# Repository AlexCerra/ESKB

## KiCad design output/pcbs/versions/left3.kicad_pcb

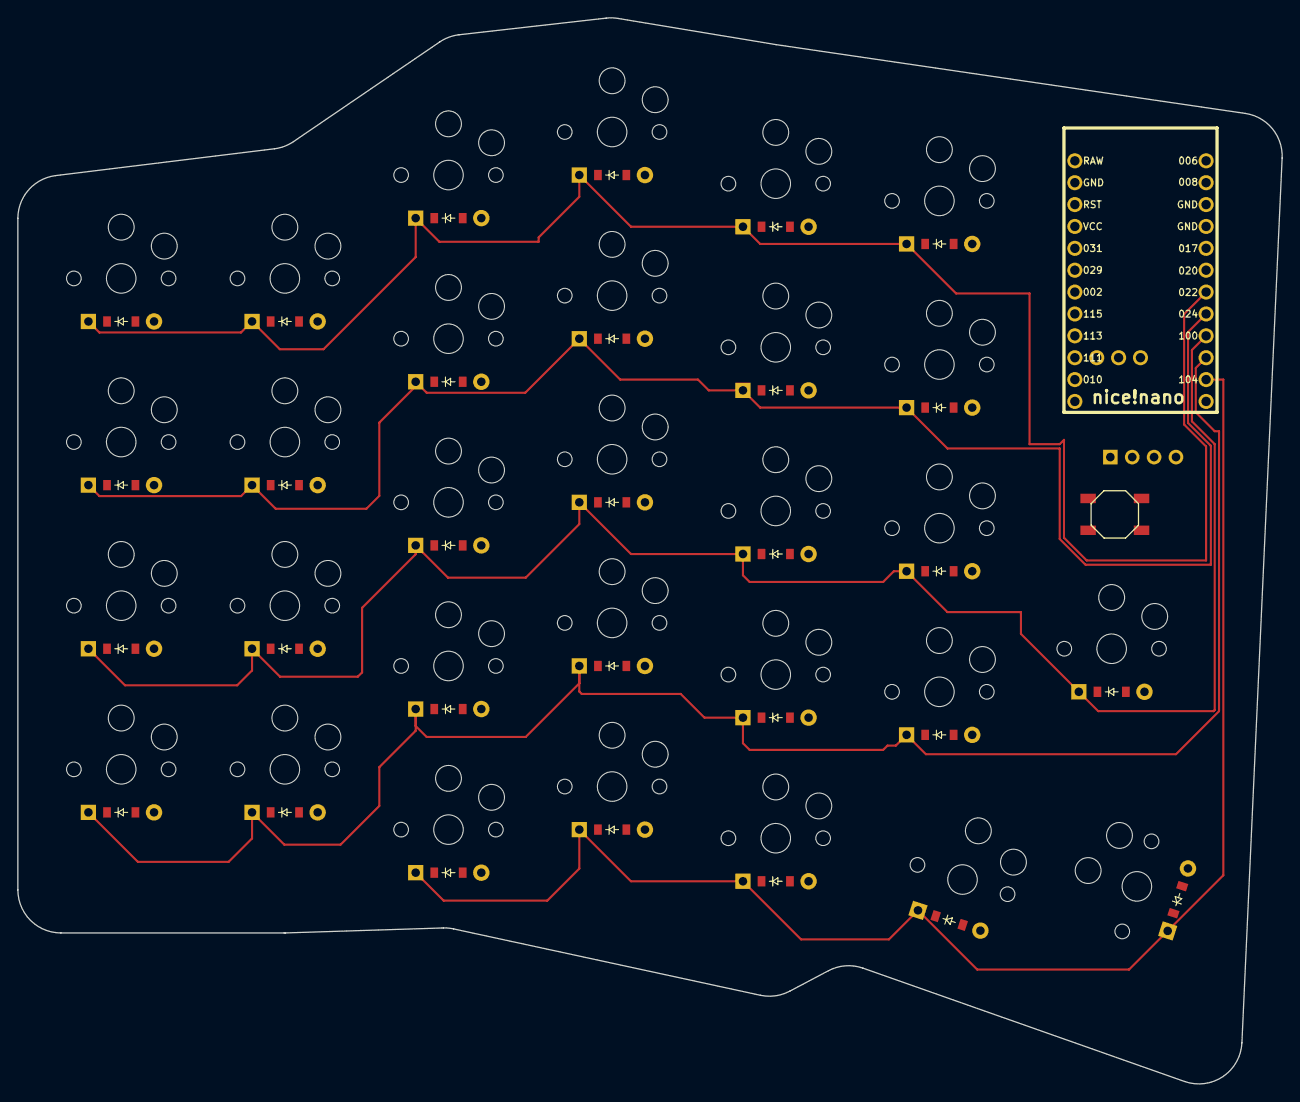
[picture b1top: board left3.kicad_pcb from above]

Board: 2 copper layers, 146.8 x 123.8 mm, 63 parts (0 on the bottom side), 39 nets.

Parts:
B1: SW_TACT_ALPS_SKQGABE010
D1, D2, D3, D4, D5, D6, D7, D8, D9, D10, D11, D12, D13, D14, D15, D16, D17, D18, D19, D20, D21, D22, D23, D24, D25, D26, D27, D28, D29, D30: ComboDiode
MCU1: nice_nano
OLED1: OLED; OLED_headers
S1, S2, S3, S4, S5, S6, S7, S8, S9, S10, S11, S12, S13, S14, S15, S16, S17, S18, S19, S20, S21, S22, S23, S24, S25, S26, S27, S28, S29, S30: PG1350

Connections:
GND: B1.1, MCU1.3, MCU1.4, MCU1.23, OLED1.1
P011: D1.1, D5.1, D10.1, D15.1, D20.1, D24.1, MCU1.10
P017: MCU1.5, OLED1.4
P020: MCU1.6, OLED1.3
P022: D4.1, D8.1, D13.1, D18.1, D23.1, D27.1, MCU1.7
P024: D3.1, D7.1, D12.1, D17.1, D22.1, D26.1, MCU1.8
P100: D2.1, D6.1, D11.1, D16.1, D21.1, D25.1, D28.1, MCU1.9
P104: D9.1, D14.1, D19.1, D29.1, D30.1, MCU1.11
VCC: MCU1.21, OLED1.2
far_cluster: D30.2, S30.2
home_cluster: D29.2, S29.2
index_bottom: D20.2, S20.2
index_home: D21.2, S21.2
index_mod: D19.2, S19.2
index_num: D23.2, S23.2
index_top: D22.2, S22.2
inner_bottom: D24.2, S24.2
inner_home: D25.2, S25.2
inner_mod_home: D28.2, S28.2
inner_num: D27.2, S27.2
inner_top: D26.2, S26.2
middle_bottom: D15.2, S15.2
middle_home: D16.2, S16.2
middle_mod: D14.2, S14.2
middle_num: D18.2, S18.2
middle_top: D17.2, S17.2
outer_bottom: D1.2, S1.2
outer_home: D2.2, S2.2
outer_num: D4.2, S4.2
outer_top: D3.2, S3.2
pinky_bottom: D5.2, S5.2
pinky_home: D6.2, S6.2
pinky_num: D8.2, S8.2
pinky_top: D7.2, S7.2
ring_bottom: D10.2, S10.2
ring_home: D11.2, S11.2
ring_mod: D9.2, S9.2
ring_num: D13.2, S13.2
ring_top: D12.2, S12.2
